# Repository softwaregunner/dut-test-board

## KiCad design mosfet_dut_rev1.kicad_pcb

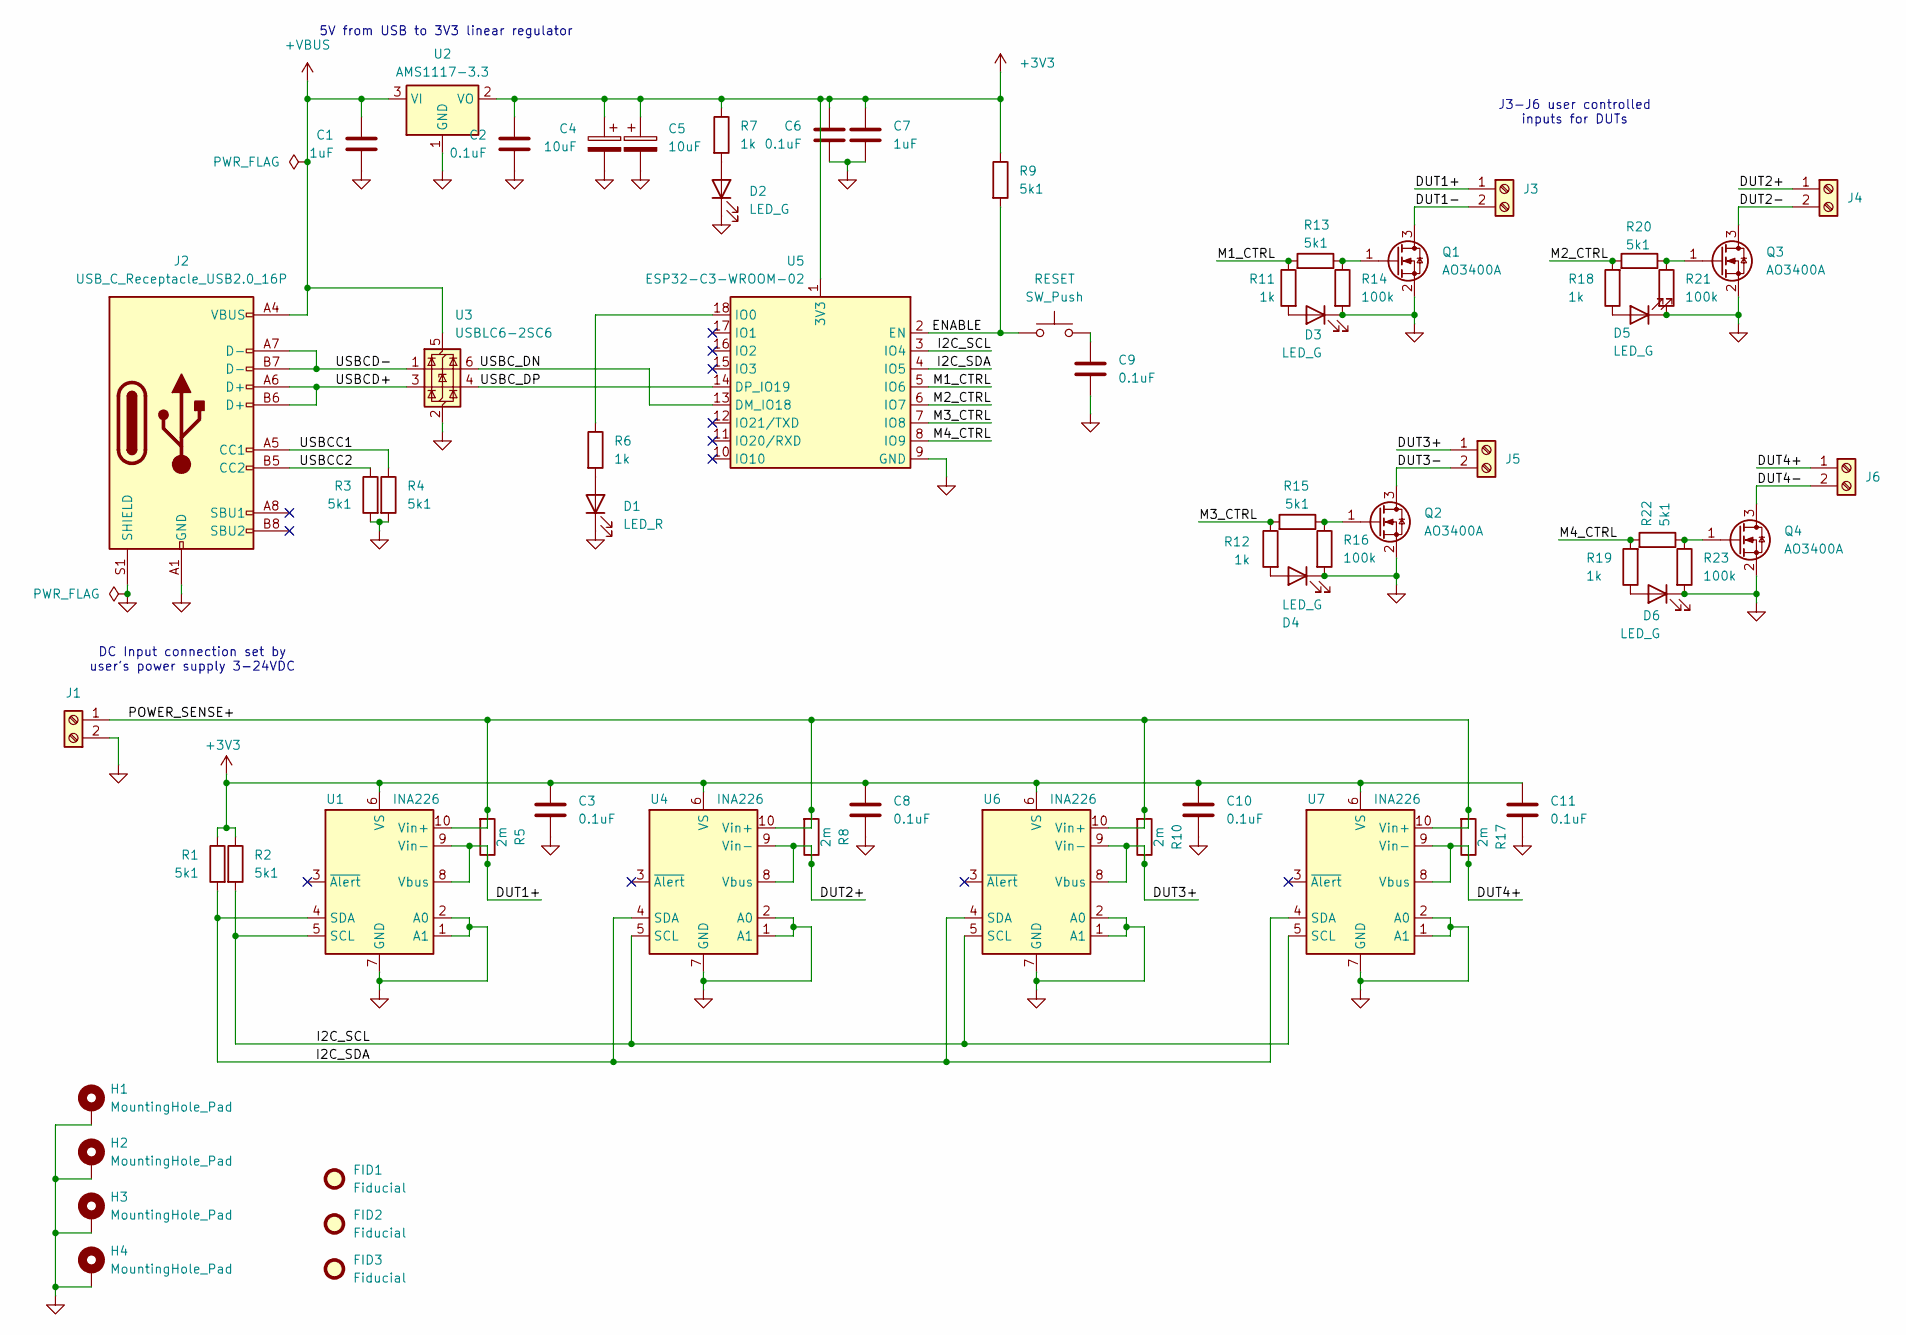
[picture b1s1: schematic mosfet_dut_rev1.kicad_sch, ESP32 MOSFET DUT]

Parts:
C1, C7: 1uF; C_0603_1608Metric; JLCPCB Part # CL10A105KB8NNNC
C2, C3, C6, C8, C9, C10, C11: 0.1uF; C_0603_1608Metric; JLCPCB Part # C14663
C4, C5: 10uF; CP_EIA-3216-18_Kemet-A; JLCPCB Part # C7171
D1: LED_R; LED_0805_2012Metric; JLCPCB Part # C84256
D2, D3, D4, D5, D6: LED_G; LED_0805_2012Metric; JLCPCB Part # C2297
FID1, FID2, FID3: Fiducial; Fiducial_1mm_Mask2mm
H1, H2, H3, H4: MountingHole_Pad; MountingHole_2.7mm_Pad_Via
J1, J3, J4, J5, J6: SCREW_TERMINAL; TerminalBlock_Phoenix_MKDS-1,5-2_1x02_P5.00mm_Horizontal; JLCPCB Part # C474881
J2: USB_C_Receptacle_USB2.0_16P; USB_C_Receptacle_GCT_USB4105-xx-A_16P_TopMnt_Horizontal; JLCPCB Part # C2765186
Q1, Q2, Q3, Q4: AO3400A; SOT-23-3; JLCPCB Part # C20917
R1, R2, R3, R4, R9, R13, R15, R20, R22: 5k1; R_0603_1608Metric; JLCPCB Part # C23186
R5, R8, R10, R17: 2m; R_2512_6332Metric; MPN HoLLR2512-3W-2mR-1%; JLCPCB Part # C2994640
R6, R7, R11, R12, R18, R19: 1k; R_0603_1608Metric; JLCPCB Part # C21190
R14, R16, R21, R23: 100k; R_0603_1608Metric; JLCPCB Part # C25803
RESET: SW_Push; SW_Push_SPST_NO_Alps_SKRK; JLCPCB Part # C720477
U1, U4, U6, U7: INA226; VSSOP-10_3x3mm_P0.5mm; JLCPCB Part # C49851
U2: AMS1117-3.3; SOT-223-3_TabPin2
U3: USBLC6-2SC6; SOT-23-6; JLCPCB Part # C2827654
U5: ESP32-C3-WROOM-02; JLCPCB Part # C2934560

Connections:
+3V3: C2.1, C3.1, C4.1, C5.1, C6.1, C7.1, C8.1, C10.1, C11.1, R1.1, R2.1, R7.1, R9.1, U1.6 (VS), U2.2 (VO), U4.6 (VS), U5.1 (3V3), U6.6 (VS), U7.6 (VS)
+VBUS: C1.2, J2.A4 (VBUS), J2.A9 (VBUS), J2.B4 (VBUS), J2.B9 (VBUS), U2.3 (VI), U3.5 (VBUS)
/DUT1+: J3.1, R5.1, U1.8 (Vbus), U1.9 (Vin-)
/DUT1-: J3.2, Q1.3 (D)
/DUT2+: J4.1, R8.1, U4.8 (Vbus), U4.9 (Vin-)
/DUT2-: J4.2, Q3.3 (D)
/DUT3+: J5.1, R10.1, U6.8 (Vbus), U6.9 (Vin-)
/DUT3-: J5.2, Q2.3 (D)
/DUT4+: J6.1, R17.1, U7.8 (Vbus), U7.9 (Vin-)
/DUT4-: J6.2, Q4.3 (D)
/ENABLE: R9.2, RESET.2, U5.2 (EN)
/I2C_SCL: R2.2, U1.5 (SCL), U4.5 (SCL), U5.3 (IO4), U6.5 (SCL), U7.5 (SCL)
/I2C_SDA: R1.2, U1.4 (SDA), U4.4 (SDA), U5.4 (IO5), U6.4 (SDA), U7.4 (SDA)
/M1_CTRL: R11.1, R13.2, U5.5 (IO6)
/M2_CTRL: R18.2, R20.2, U5.6 (IO7)
/M3_CTRL: R12.1, R15.2, U5.7 (IO8)
/M4_CTRL: R19.2, R22.2, U5.8 (IO9)
/POWER_SENSE+: J1.1, R5.2, R8.2, R10.2, R17.2, U1.10 (Vin+), U4.10 (Vin+), U6.10 (Vin+), U7.10 (Vin+)
/USBCC1: J2.A5 (CC1), R4.1
/USBCC2: J2.B5 (CC2), R3.1
/USBCD+: J2.A6 (D+), J2.B6 (D+), U3.3 (I/O2)
/USBCD-: J2.A7 (D-), J2.B7 (D-), U3.1 (I/O1)
/USBC_DN: U3.6 (I/O1), U5.13 (DM_IO18)
/USBC_DP: U3.4 (I/O2), U5.14 (DP_IO19)
GND: C1.1, C2.2, C3.2, C4.2, C5.2, C6.2, C7.2, C8.2, C9.2, C10.2, C11.2, D1.1 (K), D2.1 (K), D3.1 (K), D4.1 (K), D5.1 (K), D6.1 (K), H1.1, H2.1, H3.1, H4.1, J1.2, J2.A1 (GND), J2.A12 (GND), J2.B1 (GND), J2.B12 (GND), J2.S1 (SHIELD), Q1.2 (S), Q2.2 (S), Q3.2 (S), Q4.2 (S), R3.2, R4.2, R14.2, R16.2, R21.2, R23.2, U1.1 (A1), U1.2 (A0), U1.7 (GND), U2.1 (GND), U3.2 (GND), U4.1 (A1), U4.2 (A0), U4.7 (GND), U5.9 (GND), U5.19 (GND), U6.1 (A1), U6.2 (A0), U6.7 (GND), U7.1 (A1), U7.2 (A0), U7.7 (GND)
unnamed: C9.1, RESET.1
unnamed: D1.2 (A), R6.2
unnamed: D2.2 (A), R7.2
unnamed: D3.2 (A), R11.2
unnamed: D4.2 (A), R12.2
unnamed: D5.2 (A), R18.1
unnamed: D6.2 (A), R19.1
unnamed: Q1.1 (G), R13.1, R14.1
unnamed: Q2.1 (G), R15.1, R16.1
unnamed: Q3.1 (G), R20.1, R21.1
unnamed: Q4.1 (G), R22.1, R23.1
unnamed: R6.1, U5.18 (IO0)

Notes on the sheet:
5V from USB to 3V3 linear regulator
J3-J6 user controlled inputs for DUTs
DC Input connection set by user's power supply 3-24VDC

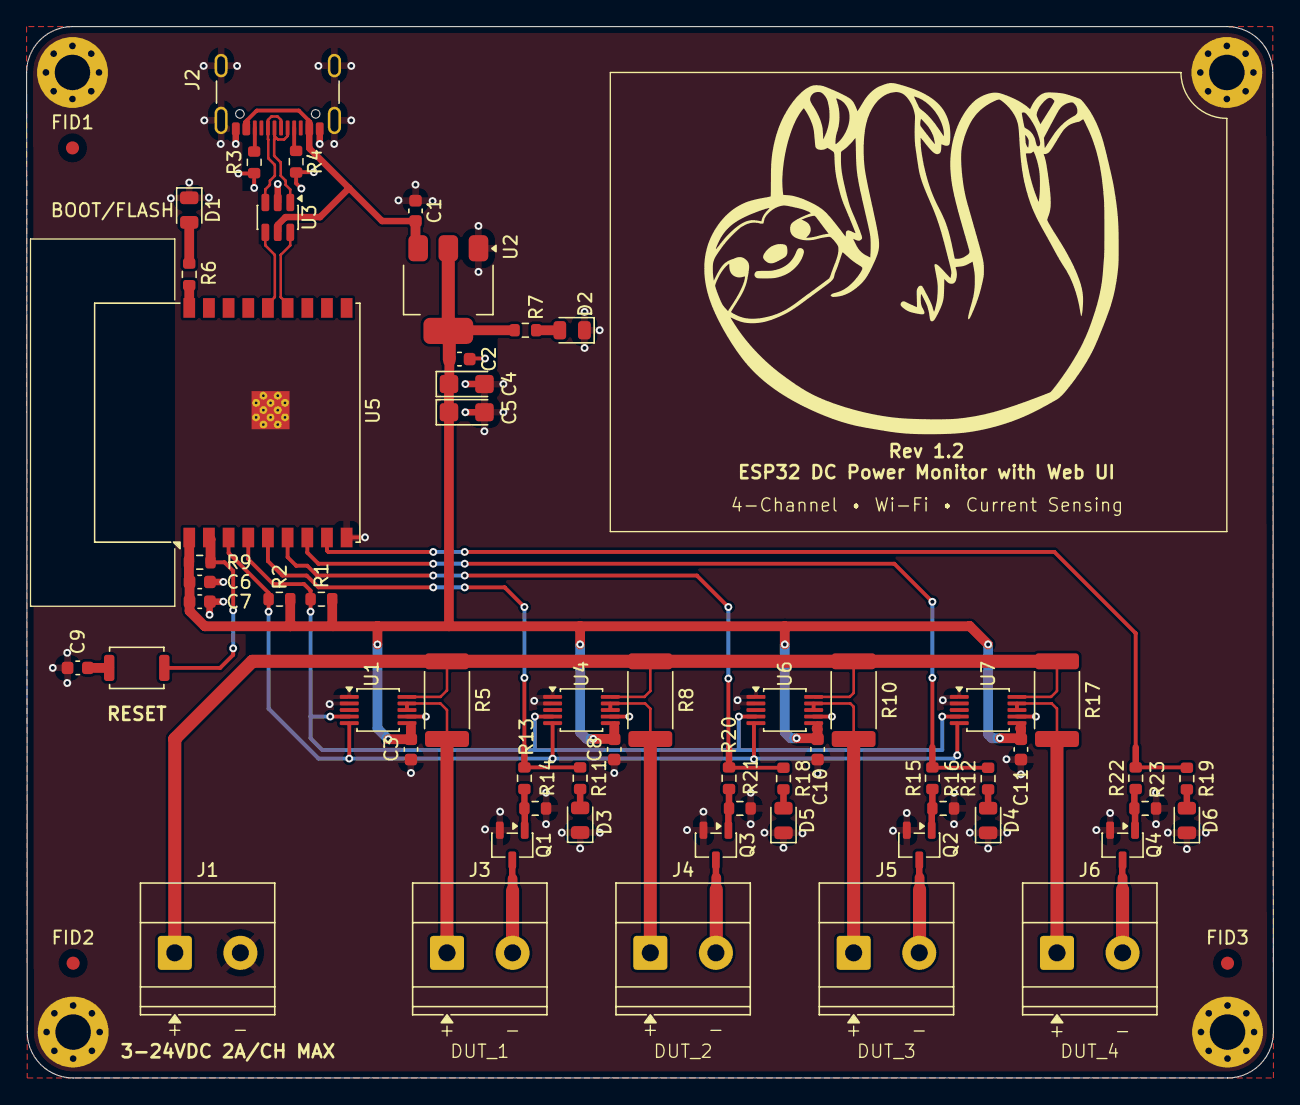
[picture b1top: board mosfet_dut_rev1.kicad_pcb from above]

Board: 2 copper layers, 95.0 x 80.2 mm, 65 parts (0 on the bottom side), 37 nets.

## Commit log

2026-01-09 First commit Revision 1.0
2026-01-09 Initial KiCad project
2026-01-09 Add KiCad gitignore
2026-01-09 Fix gitignore and remove tracked KiCad backups
2026-01-09 Revision 1.0
2026-01-09 Swapping to basic jlcpcb parts APK2112K-3.3 -> ME6211C33M5
2026-01-09 MUX/Shunts schematic wiring
2026-01-10 Rev 1.1: Schematic Complete + BOM + JLCPCB Part Numbers
2026-01-10 Rev 1.1: Colored my nets
2026-01-10 Rev 1.1: Final Component Schematic + BOM
2026-01-10 Rev 1.1: Board placement and rough tracks
2026-01-11 Rev 1.1: Final
2026-01-13 Rev 1.2 Final
